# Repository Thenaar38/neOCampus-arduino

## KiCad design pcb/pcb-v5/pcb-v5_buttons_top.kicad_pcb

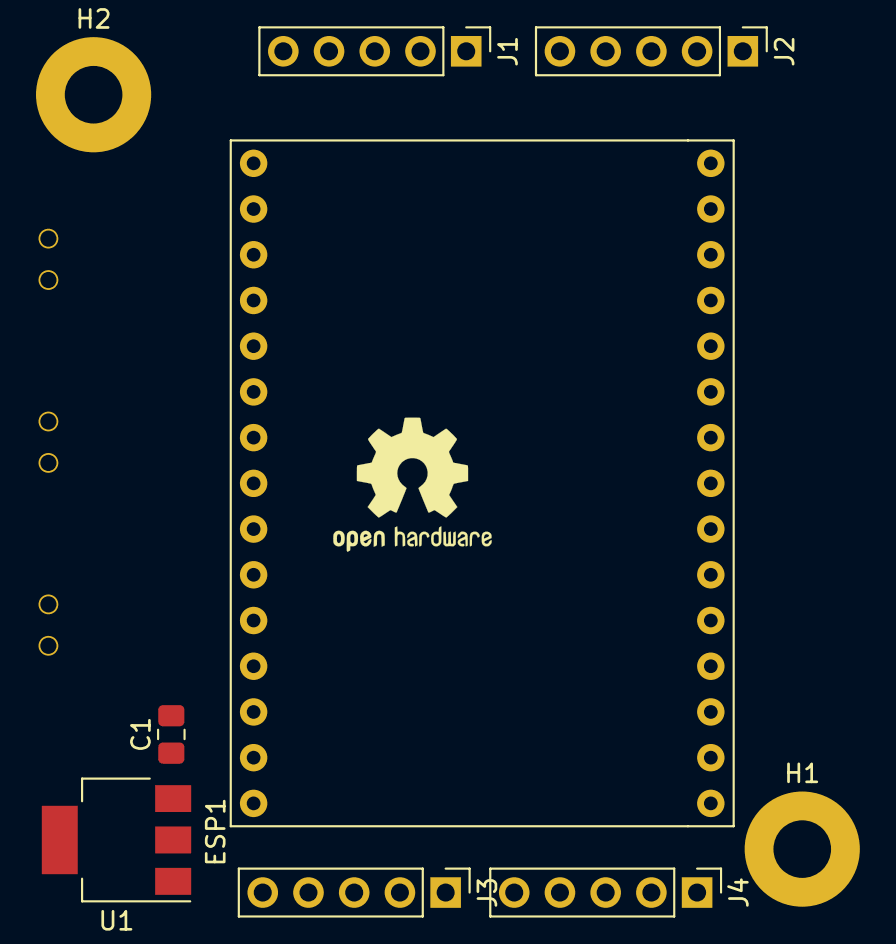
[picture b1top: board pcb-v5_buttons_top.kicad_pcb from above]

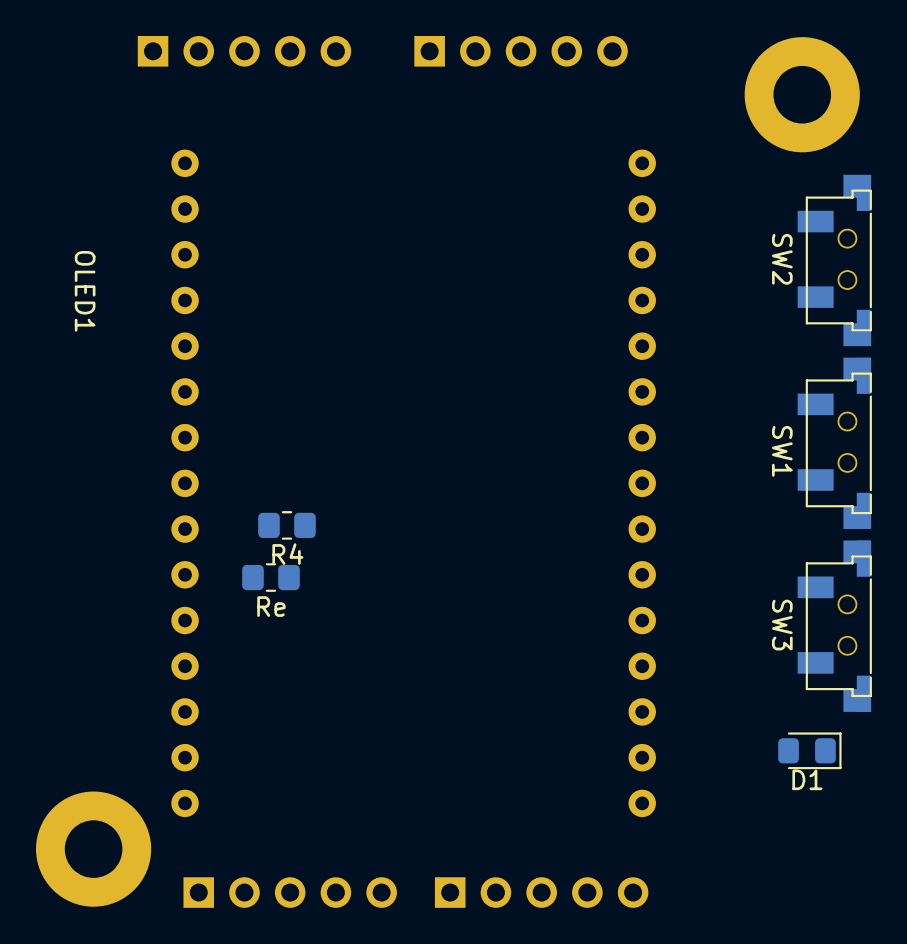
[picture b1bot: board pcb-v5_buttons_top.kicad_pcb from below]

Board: 2 copper layers, 16 parts (7 on the bottom side), 10 nets, no tracks yet.

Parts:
C1: 10µF; C_0805_2012Metric_Pad1.18x1.45mm_HandSolder
D1: LED; LED_0805_2012Metric_Pad1.15x1.40mm_HandSolder
ESP1: ESP32; ESP32_30_pins
H1, H2: MountingHole_Pad; MountingHole_3.2mm_M3_Pad
J1, J2, J3: Conn_01x05_Female; PinHeader_1x05_P2.54mm_Vertical
J4: Conn_01x05_Male; PinHeader_1x05_P2.54mm_Vertical
OLED1: OLED_1.3
R4: 220; R_0805_2012Metric_Pad1.20x1.40mm_HandSolder
Re: 220; R_0805_2012Metric_Pad1.20x1.40mm_HandSolder
SW1, SW2, SW3: G71Y; G71Y_µsw_smd
U1: AMS1117-3.3; SOT-223-3_TabPin2

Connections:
3V3: J1.5, J2.5, J3.5, SW1.1, SW2.1, SW3.1, U1.2
GND: C1.2, ESP1.1, H1.1, H2.1, J1.4, J2.4, J3.4, J4.3, SW1.3, SW2.3, SW3.3, U1.1
GPIO_32: ESP1.12, SW2.2
GPIO_33: ESP1.13, SW1.2
INT: ESP1.11, J1.1, J2.1, J3.1, J4.1
SCL: ESP1.39, J1.3, J2.3, J3.3
SDA: ESP1.42, J1.2, J2.2, J3.2
U2_RX: ESP1.25, J4.4
U2_TX: ESP1.27, J4.5
VIN: C1.1, D1.2, ESP1.2, J4.2, U1.3

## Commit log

2021-01-20 PCB-V5 creation
    First templates created for ESP32, OLED screen and SDS011 sensor on the scematics
2021-01-20 PCB-V5 updated
    Added 2 mounting holes and 2x4pins connectors
2021-01-20 PCB-V5 update
    PCB updated for presentation
2021-01-21 PCB-V5 update
    Added ESP32 3D model
2021-01-27 ESP32 board update
    Added 3 buttons and 1 LED.
    Added metallized AMS1117 back
2021-01-27 PCB-V5 update
    Updated after meeting
2021-01-27 PCB-V5 update
    Changed buttons and pins location.
2021-01-28 PCB-V5
    Updated after meeting with client
2021-01-29 PCB-V5 update
    Panelization v1
2021-01-30 PCB-V2 update
    Added OSHW logo on both boards.
    Upgraded power lines size to 0.6604.
    Added every needed screen printings (VCC,SDA,SCL,...)
2021-01-30 PCB-V5 update
    Panelized version 1.0.0
2021-01-30 PAUL
2021-02-04 resistance+M2SIAME
